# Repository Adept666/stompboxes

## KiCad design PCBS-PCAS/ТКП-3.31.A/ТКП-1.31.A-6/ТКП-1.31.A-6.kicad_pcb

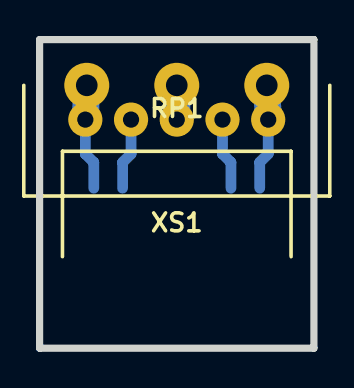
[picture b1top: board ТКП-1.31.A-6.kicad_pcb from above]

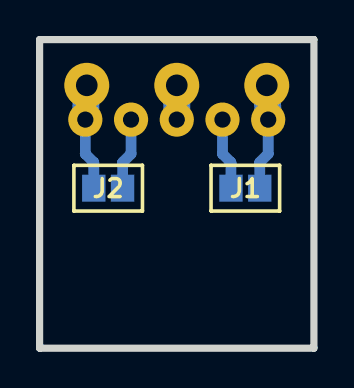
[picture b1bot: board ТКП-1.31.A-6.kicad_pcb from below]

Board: 2 copper layers, 15.2 x 17.1 mm, 4 parts (2 on the bottom side), 5 nets.

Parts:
J1: J1; J-SB-0805-2
J2: J2; J-SB-0805-2
RP1: B100K; RP-PDB181-K-20-P-CIRCULAR
XS1: PBS-05R; CON-PBS-05R-CIRCULAR

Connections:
unnamed: J1.1, RP1.3, XS1.1
unnamed: J1.2, XS1.2
unnamed: J2.1, XS1.4
unnamed: J2.2, RP1.1, XS1.5
unnamed: RP1.2, XS1.3

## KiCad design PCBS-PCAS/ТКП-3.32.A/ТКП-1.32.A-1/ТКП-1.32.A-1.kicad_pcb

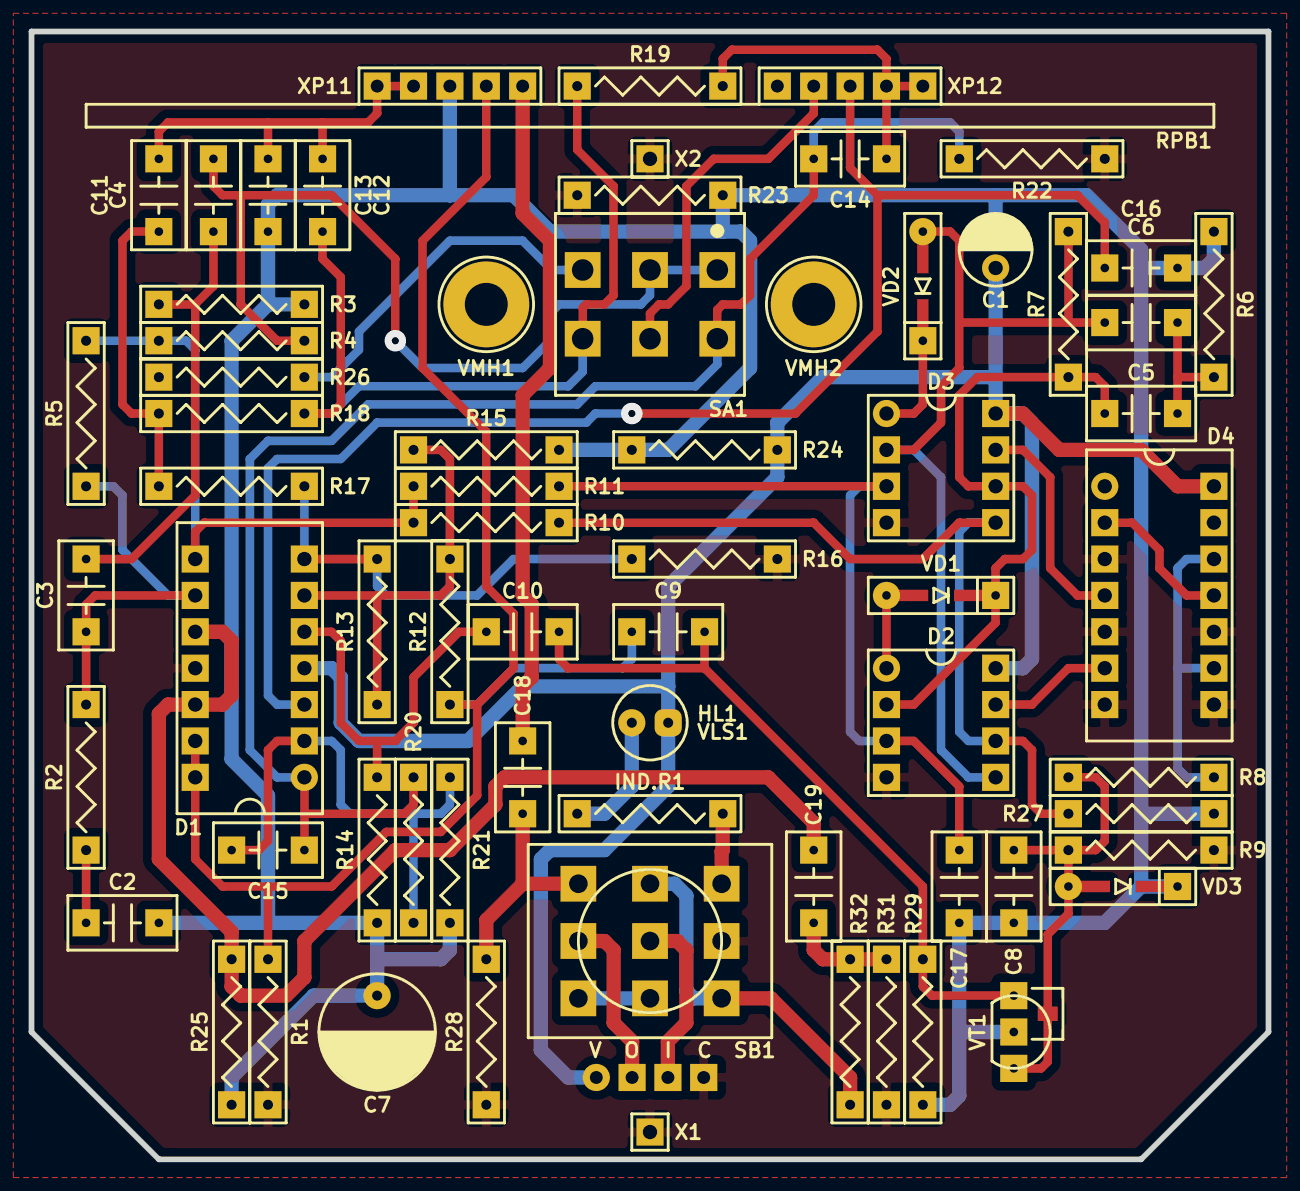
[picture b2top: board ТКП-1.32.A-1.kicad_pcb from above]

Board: 2 copper layers, 86.4 x 78.7 mm, 71 parts (1 on the bottom side), 44 nets.

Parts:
C1: 336; CP-RADIAL-D05.0-P02.0-CLS
C2, C5, C6, C9, C10, C18, C19: 104; C-DISK-D04.2-T03.0-P05.08-d0.5
C3, C4, C8, C13, C15, C16, C17: 223; C-DISK-D04.2-T03.0-P05.08-d0.5
C7: 477; CP-RADIAL-D08.0-P03.5-d0.6
C11, C12: 154; C-DISK-D04.2-T03.0-P05.08-d0.5
C14: 473; C-DISK-D04.2-T03.0-P05.08-d0.5
D1: 324; P-DIP-14
D2, D3: 4558; P-DIP-08
D4: 4013; P-DIP-14
HL1: FYL-5013URC; LED-ROUND-05.0-UNI-SH-SPACER-PNL-5.3
IND.R1: 472; R-MFR-25
R1, R10, R11, R12, R16, R22: 103; R-MFR-25
R2, R14, R25, R27: 104; R-MFR-25
R3, R19: 183; R-MFR-25
R4, R13, R23, R24: 153; R-MFR-25
R5: 334; R-MFR-25
R6: 471; R-MFR-25
R7: 184; R-MFR-25
R8, R9, R15: 273; R-MFR-25
R17, R18: 472; R-MFR-25
R20, R21: 473; R-MFR-25
R26: 681; R-MFR-25
R28, R31: 225; R-MFR-25
R29: 154; R-MFR-25
R32: 102; R-MFR-25
RPB1: A100K-B100K-B100K; RPB-1590BB2-18-3x17-1.6-PNL-7.4-2.8
SA1: MTS-202-A2; SW-MTS-202-A2-2.5-PNL-6.0
SB1: PBS-24-302SP; SW-PBS-24-302SP-2.5-PNL-13.0
VD1, VD2, VD3: 4148; P-SOD-123-OR-DO-35-V1
VE1: 1590BB2; 1590BB2_A1
VLS1: BR-12.7; VLS-BR
VMH1, VMH2: DI5M3x18; VMH-STA-DA5-PNL-3.0
VT1: 5457; P-SOT-23-D-S-G-OR-TO-92-D-S-G
X1, X2: COM; CON-PAD-S-1.0-1.9
XB1: 1590BB2 Connector Board Extended; XB-1590BB2-EXTENDED
XP1: B4B-XH-A; CON-XH-B4B-A

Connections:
/BF-IN: C12.1, R18.2, R19.1, SA1.NO2
/BF-OUT: C14.1, C15.1, D1.1, R20.2, R22.2, SA1.NC2
/DRY: C9.1, D1.13, D1.14, R1.2, R12.1, RPB1.21
/IN-CIR: R32.1, SB1.NC3, SB1.NO2
/IN-CON: SB1.COM2, XP1.3
/LED: IND.R1.1, SB1.NO3
/OUT-CIR: C18.2, R28.2, SB1.NO1
/OUT-CON: SB1.COM1, XP1.2
/RANGE: C4.2, R4.1, SA1.COM1, SA1.NC1
/RANGE-HIGH: R26.2, SA1.NO1
/RESET: D3.7, D4.4
/SET: D2.7, D4.6
/WET: RPB1.23, SA1.COM2
COM: C7.-, D1.11, D2.4, D3.4, D4.3, D4.5, D4.7, D4.8, D4.10, R1.1, R9.1, R16.1, R22.1, R23.1, R26.1, R28.1, R31.1, SB1.COM3, X1.1, X2.1, XP1.4
unnamed: C2.1, R2.1
unnamed: C3.1, D1.9, R2.2, R5.1
unnamed: C3.2, C4.1, R3.2
unnamed: C5.1, D2.2, D3.6, R7.2, VD1.C
unnamed: C5.2, C6.1, R6.2
unnamed: C6.2, D2.5, D3.2, R7.1, VD2.A
unnamed: C8.1, R8.1, R9.2, VD3.A, VT1.G
unnamed: C9.2, C10.1, R29.2, VT1.D
unnamed: C10.2, D1.5, R14.2
unnamed: C11.1, R17.2, R18.1
unnamed: C11.2, C12.2, C13.1, RPB1.12, RPB1.13
unnamed: C14.2, R19.2, RPB1.31, RPB1.32
unnamed: C15.2, D1.2, R20.1, R21.2
unnamed: C16.1, D1.3, RPB1.33
unnamed: C17.1, D2.3, D3.3, R11.1
unnamed: C18.1, RPB1.22
unnamed: C19.1, R31.2, R32.2
unnamed: C19.2, D1.10, D1.12, R25.2
unnamed: D1.6, R12.2, R13.1, R15.2
unnamed: D1.7, R13.2, R16.2, R17.1
unnamed: D1.8, R4.2, R5.2, R10.2, R11.2
unnamed: D2.1, VD1.A
unnamed: D2.6, D3.5, R10.1, R27.2
unnamed: D3.1, VD2.C
unnamed: D4.2, D4.11
unnamed: D4.9, D4.12, R8.2
unnamed: HL1.C, IND.R1.2
unnamed: SB1.NC1, SB1.NC2
V: C1.+, D1.4, D2.8, D3.8, D4.14, HL1.A, R24.2, XP1.1
VREF: C1.-, C2.2, C7.+, C8.2, C13.2, C16.2, C17.2, R3.1, R6.1, R14.1, R15.1, R21.1, R23.2, R24.1, R25.1, R27.1, R29.1, RPB1.11, VD3.C, VT1.S

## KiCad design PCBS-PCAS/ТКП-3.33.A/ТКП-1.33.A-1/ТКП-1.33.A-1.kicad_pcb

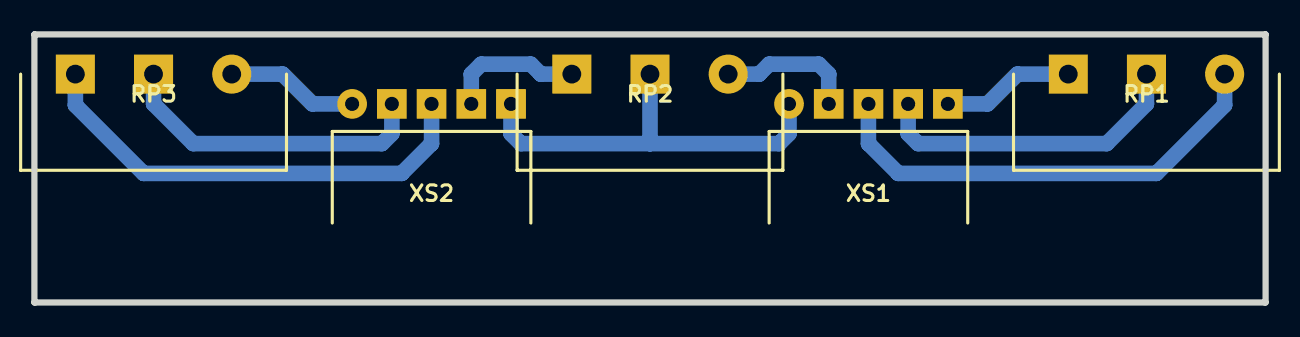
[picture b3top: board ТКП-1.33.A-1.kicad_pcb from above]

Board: 2 copper layers, 78.7 x 17.1 mm, 5 parts (0 on the bottom side), 9 nets.

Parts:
RP1: RP1: A100K; RP-PDB181-K-20-P
RP2: RP2: B100K; RP-PDB181-K-20-P
RP3: RP3: B100K; RP-PDB181-K-20-P
XS1, XS2: PBS-05R; CON-PBS-05R

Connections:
unnamed: RP1.1, XS1.3
unnamed: RP1.2, XS1.4
unnamed: RP1.3, XS1.5
unnamed: RP2.1, XS1.2
unnamed: RP2.2, XS1.1, XS2.5
unnamed: RP2.3, XS2.4
unnamed: RP3.1, XS2.1
unnamed: RP3.2, XS2.2
unnamed: RP3.3, XS2.3

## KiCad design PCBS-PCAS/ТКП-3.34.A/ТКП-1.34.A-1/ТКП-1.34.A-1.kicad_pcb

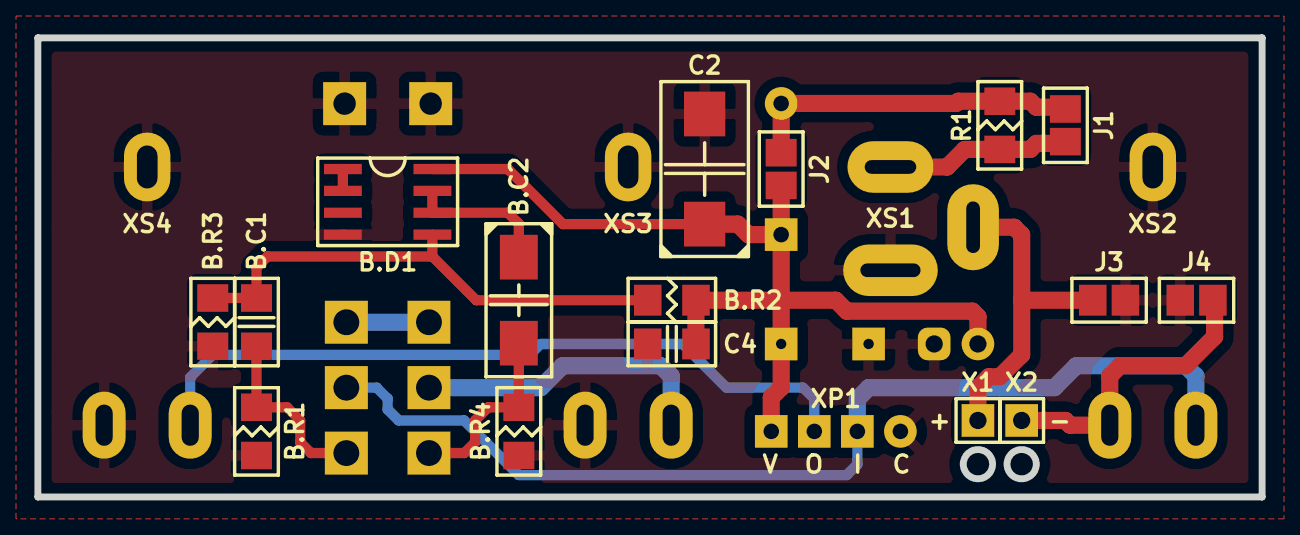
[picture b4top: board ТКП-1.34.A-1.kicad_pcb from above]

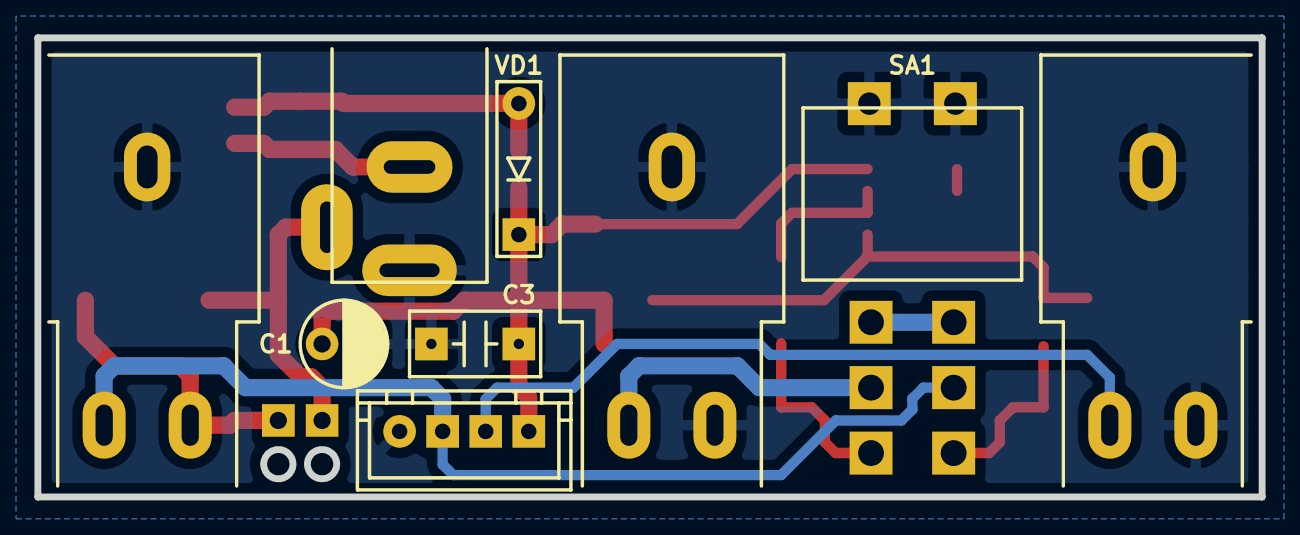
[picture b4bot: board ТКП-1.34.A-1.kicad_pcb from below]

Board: 2 copper layers, 71.1 x 26.7 mm, 26 parts (9 on the bottom side), 15 nets.

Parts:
B.C1: 105; C-SM-1206
B.C2: 106; CP-CTSMD-C
B.D1: 4558; P-SO-08
B.R1: X; R-SM-1206
B.R2, B.R3, B.R4: 105; R-SM-1206
C1: 107; CP-RADIAL-D05.0-P02.0-CLS
C2: 107; CP-CTSMD-D
C3: 104; C-DISK-D04.2-T03.0-P05.08-d0.5
C4: 104; C-SM-1206
GB1: X; B-PP3-HV
J1: J1; J-SB-1206-2
J2: J2; J-SB-1206-2
J3: J3; J-SB-1206-2
J4: J4; J-SB-1206-2
R1: 470; R-SM-1206
SA1: MTS-202-C4; SW-MTS-202-C4-2.5
VD1: X; P-DO-41
X1, X2: X; CON-PAD-S-1.0-1.9
XP1: B4B-XH-A; CON-XH-B4B-A
XS1: DC-005; CON-DC-005-9V-OVAL
XS2: PJ-651A-01; CON-PJ-651A-01-IN-OVAL
XS3: PJ-651A-01; CON-PJ-651A-01-DRY-OUT-OVAL
XS4: PJ-651A-01; CON-PJ-651A-01-OUT-OVAL

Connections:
/BUF-IN: B.C1.1, B.R1.2, SA1.NC1
/BUF-OUT: B.C2.-, B.R4.2, SA1.NC2
/DRY-OUT-CON: SA1.COM2, XS3.T
/IN-CON: SA1.COM1, XP1.2, XS2.T
/OUT-CON: XP1.3, XS4.T
/PP3-NEG: J4.1, X2.1, XS2.R
/PP3-POS: J3.1, X1.1, XS1.SN
COM: B.D1.4, B.R1.1, B.R3.1, B.R4.1, C1.-, C2.-, C3.2, C4.2, J3.2, J4.2, SA1.0, XP1.1, XS1.C, XS2.S, XS3.R, XS3.S, XS4.R, XS4.S
unnamed: B.C1.2, B.D1.5, B.R2.1, B.R3.2
unnamed: B.C2.+, B.D1.6, B.D1.7
unnamed: B.D1.1, B.D1.2
unnamed: J1.1, R1.1, XS1.S
unnamed: J1.2, J2.1, R1.2, VD1.A
unnamed: SA1.NO1, SA1.NO2
V: B.D1.8, B.R2.2, C1.+, C2.+, C3.1, C4.1, J2.2, VD1.C, XP1.4

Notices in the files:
PCBS-PCAS/ТКП-3.31.A/ТКП-1.31.A-6/ТКП-1.31.A-6.kicad_pcb:
This project is licensed under GNU General Public License v3.0 or later
